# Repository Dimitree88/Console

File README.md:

# CONSOLE — Reference Specification

> Analog mixing console design — full signal-flow reference and
> implementation record. This is a multi-file documentation project;
> this README is the entry point.
>
> **For Claude sessions:** working rules and session-start procedure
> live in `CLAUDE.md`, which is loaded automatically.

---

## What this project is

CONSOLE is a fully analog mixing console. 24 mono input channels,
**4 stereo AUX returns**, 3 stereo groups, 4 AUX masters, CUE master,
Main Mix master with parallel SSL-style bus compression, monitor
section with AFL/PFL solo logic.

Firmware is out of scope; this documents the analog signal flow and
the implementation decisions made during circuit design.

---

## Mental model (one paragraph)

CONSOLE is a 24+4+3 analog desk (24 mono channels, 4 stereo AUX
returns, 3 stereo sub-groups) feeding a Main stereo bus with
parallel SSL-style compression. Channel strips follow a conventional
flow (balanced in → gain → HPF → insert → meter and PFL taps →
MUTE electronic switch → fader → +10 dB post-amp → pan → routing)
with two distinctive design choices: (1) dual balanced inputs A/B
with a full-differential Channel Output from Input A for ADC tracking;
(2) every channel has 4 AUX sends implemented as dual-gang pots that
simultaneously drive a pre-fader and a post-fader mono bus, giving
8 AUX buses total. The 4 stereo AUX returns are routing-only
(no Post-Fader Output to the outside, no Insert, no AUX send) — they
contribute only to internal buses (Main / Groups / AFL / CUE / PFL
stereo). Groups offer per-AUX split-or-mono mode switches so a
stereo group can feed stereo AUX pairs either as L/R split or as
mono premix. The master section's distinguishing features are the
parallel compression on the main bus (dry fader + SSL-style
compressor + wet fader → summed output) and an "in front balance"
pot that mixes an attenuated main mix behind the AFL so the engineer
always hears the context. Digital control is limited to hard-muting /
enabling electronic switches for ACTIVE, SOLO, and AFL — no VCAs,
no recall, no automation. Talkback, tone oscillators, and master
master meters are deliberately absent.

---

## File map

| File | Contents |
|------|----------|
| `CLAUDE.md` | working rules for Claude — required reading at session start, loaded automatically |
| `README.md` | this file — entry point, file map, project status snapshot |
| `00-conventions.md` | design conventions + electrical/implementation conventions (power supplies, grounds, packages, default audio opamp, default topologies for EMI filter, impedance-balanced output, switches+LEDs, …) |
| `01-bus-inventory.md` | enumeration of every bus in the console (stereo + mono) and what feeds each one |
| `02-mono-channel.md` | §2 — mono input channel signal flow + Implementation details (Blocks 1, 2, …) |
| `03-aux-return.md` | §3 — stereo AUX returns (×4, identical) |
| `04-group.md` | §4 — stereo groups (×3) |
| `05-aux-master.md` | §5 — AUX master (×4) |
| `06-cue-master.md` | §6 — CUE master |
| `07-main-mix.md` | §7 — Main Mix master + parallel compression |
| `08-monitor.md` | §8 — Master monitor section |
| `09-not-present.md` | §9 — features deliberately NOT in CONSOLE |
| `10-open-tbd.md` | §10 — items deliberately unresolved at this stage |
| `11-digital-io.md` | §11 — running count of relays, LEDs, and pushbuttons; keep in sync with design changes |

(Sections §11 "Counts" lives at the end of `01-bus-inventory.md`.
The one-paragraph mental model lives at the top of this README.)

---

## Section file structure

Every main section file (`02-mono-channel.md` through `08-monitor.md`)
contains both the **conceptual signal flow** description and an
**Implementation details** subsection. Implementation details grow
over time as concrete circuit choices are made, organized into
"Blocks" (Block 1, Block 2, …) corresponding to chunks of the
signal path that were finalized in a single conversation. The Block
template and editing rules live in `CLAUDE.md`.

---

## Project status snapshot

(Update this section briefly at the end of major conversations, so
future Claude can immediately see where things stand.)

- Mono channel: signal flow conceptually complete. Implementation:
  - Block 1 (input stage → SOURCE switch + DIRECT OUT
    SELECT relay on input PCB) FINALIZED — SOURCE
    relay-driven (AGQ210A03 latching) with momentary pushbutton +
    firmware bipolar pulse; primary motivation: enables global
    master A/B flip across all 24 channels. Channel Output SELECT
    relay added: makes the Channel Output TRS jack switchable between
    Input A full-differential and channel PRE/POST impedance-
    balanced signal (see Block 8).
  - Block 2 (HPF + Insert Send/Return + jack PCB) FINALIZED.
  - Block 3 (meter buffer concept + PFL switch + MUTE) FINALIZED —
    MUTE relay (AGQ210A03) now configured **series + shunt** (contact
    set 1 = series switch, contact set 2 = shunt PRE-FADER to AGND
    when muted), replacing the earlier paralleled-contacts approach.
    Meter buffer implementation (NE5532 + DG419) finalized in Block 10.
  - Block 4 (pre-fader node + fader PCB + post-fader amp +10 dB +
    AUX/CUE pre & post sends) FINALIZED.
  - Block 5 (active pan, Self-style) FINALIZED — Self canonical
    values (R_FB = 2.2 kΩ, center dip ≈ 4.5 dB).
  - Block 6 (post-pan 2-gang × 4-pos routing rotary) topology
    defined; bus summing resistor values TBD together with §04 / §07.
  - Block 7 (AFL switch) FINALIZED — tap at post-pan opamp output;
    NC to AGND (constant termination, click-free); NO to AFL bus.
    Summing resistor values deferred to §08.
  - Block 8 (OUT-PRE/POST switch + switchable Channel Output)
    IN-PROGRESS — 75R taps from pre-MUTE and POST-FADER nodes;
    mechanical PRE-POST selector; 2-pin connector to input PCB;
    Channel Output SELECT relay on input PCB. Front-panel control:
    latching DPDT pushbutton ("DIR/PROC"), sec. 2 → indicator LED
    (LED chain confirmed). Sec. 1 → digital/driver board; MCU GPIO
    or direct-to-driver TBD (see `10-open-tbd.md`). Cold dummy
    network TBD.
  - Block 10 (dual meter buffers) FINALIZED — SOURCE relay
    contact set 2 (wired complementary to set 1) delivers the
    inactive receiver directly to the meter buffer, no additional
    electronic switch; TL072 dual JFET opamp buffers active
    (pre-MUTE) and inactive meter signals; 3-pin connector to meter
    bridge PCB. SOURCE LEDs now MCU GPIO driven (+2 GPIO
    output per channel vs. relay-contact).
- AUX returns: 4 channels, all identical, conceptual stage. ACTIVE
  and AFL switching elements fixed as AGQ210A03 (1 relay
  per function, handling L+R on its two contact sets).
- Groups: same — ACTIVE and AFL fixed as AGQ210A03.
- Master monitor: source-select (§8.1) and Solo summer AFL/PFL
  alternation (§8.2) fixed as AGQ210A03. Other stages still
  conceptual.
- All other sections (AUX/CUE/Main masters): still conceptual.
- Global conventions: established (power, grounds, packages, default
  audio opamp **NE5532**, **standard signal relay
  AGQ210A03** (Panasonic, 1-coil latching, 3 V coil), EMI filter,
  sleeve termination, impedance-balanced output topology,
  front-panel switches with LEDs, per-PCB local bulk decoupling on
  power rails). Selective upgrade to OPA1642 / OPA1656 in specific
  positions is identified as a budget-review item — see
  `10-open-tbd.md`.
- Relay infrastructure: coil supply rail settled (+3.3 V direct);
  driver partitioning settled (per-PCB stackable two-board pattern
  per `00-conventions.md` — audio PCB carries only the relay coil
  via a 3-pin connector, lower stackable PCB carries all logic).
  Total relay count: **112** (24 channels × 4 + 4 AUX returns × 2 +
  3 groups × 2 + 2 master monitor). Coil bipolar driver IC and
  master-output hard-mute for firmware boot init still tracked as
  design-phase open issues in `10-open-tbd.md`.
- Fader PCB partitioning: settled at **2 channels per fader PCB**
  (12 fader PCBs total). Input PCB partitioning still TBD.
- Front-panel channel buttons (§2.11): defined — 4 pushbuttons per
  channel: SOURCE (Pattern B, relay-contact LED), plus
  ACTIVE (orange), SOLO (red), REC (red) all Pattern C
  (integrated LED, MCU GPIO in + out). SOLO drives AFL relay + SIP
  option; REC MIDI-only, no audio relay. Per-channel digital
  I/O: 4 GPIO inputs (buttons) + 3 GPIO outputs (LEDs) +
  relay coil drivers via dedicated ICs.

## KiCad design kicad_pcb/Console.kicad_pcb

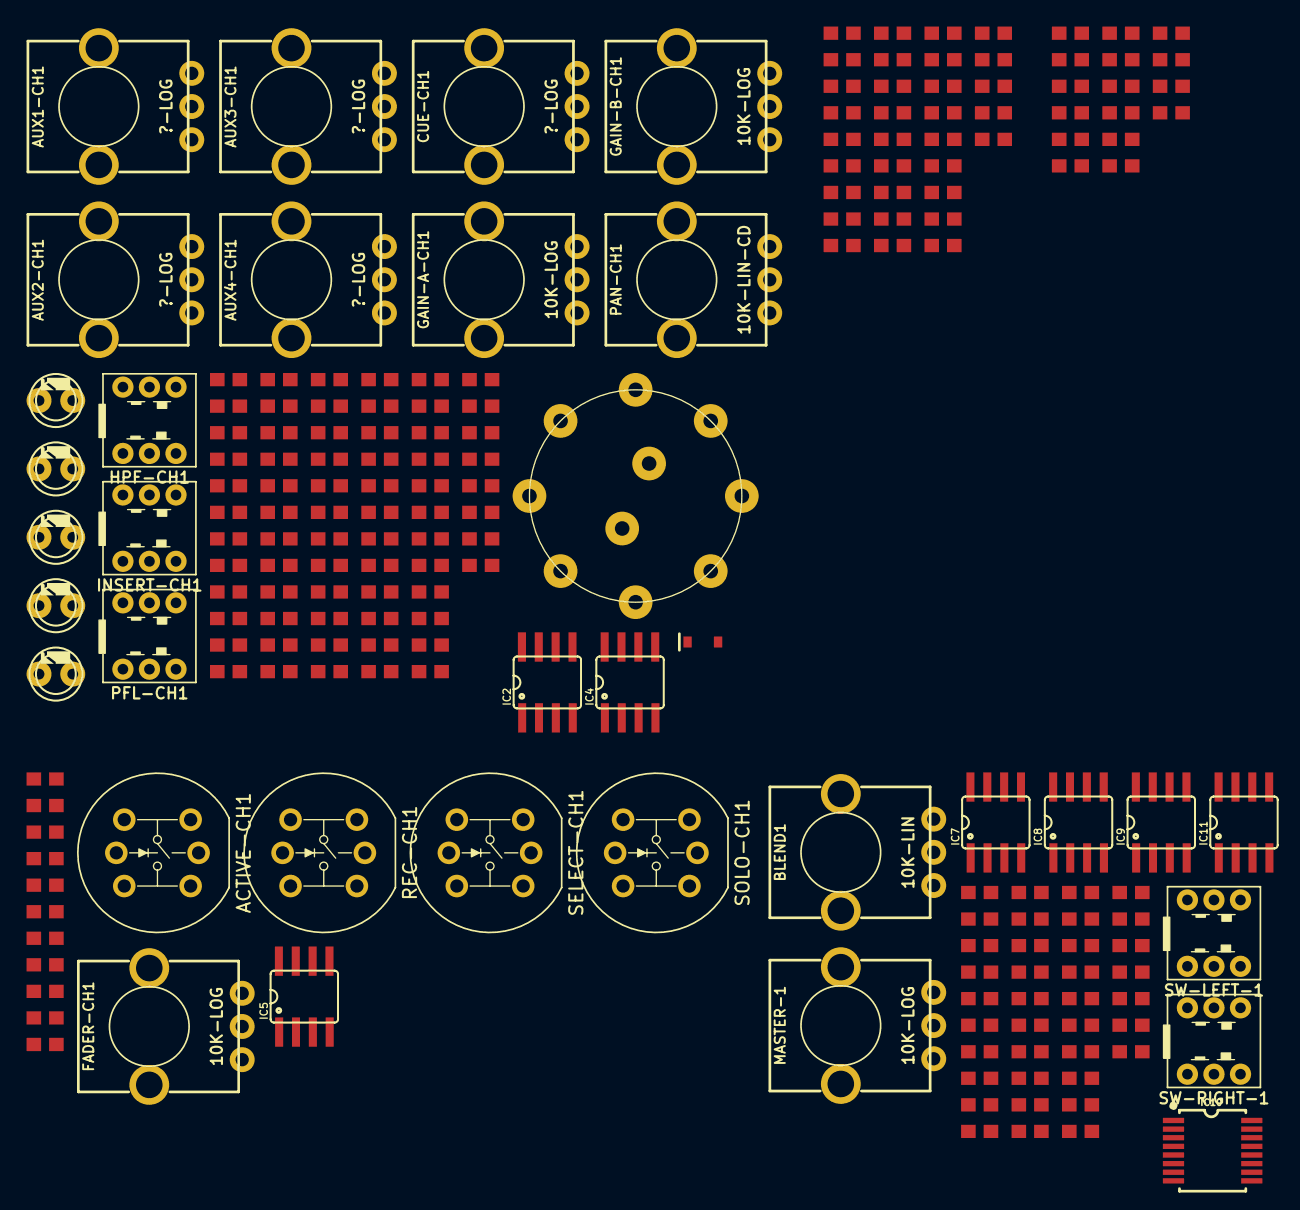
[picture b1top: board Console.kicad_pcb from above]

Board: 2 copper layers, 199 parts (0 on the bottom side), 112 nets, no tracks yet.

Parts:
ACTIVE-CH1: KS-01 yellow; KS-01
AUX1-CH1, AUX2-CH1, AUX3-CH1, AUX4-CH1: ?-LOG; POTENTIOMETER-9MM
BLEND1: 10K-LIN; POTENTIOMETER-9MM
C1, C2, C4, C5, C10, C11, C13, C14, C29, C30, C32, C33, C83, C84, C86, C87, C89, C90, C92, C93: 470pF; 0603
C3, C6, C9, C12, C28, C31, C82, C85, C88, C91: 47pF; 0603
C36, C37, C53: 100pF; 0603
C39, C40, C41: 220nF; 0603
C43, C44, C45, C46, C47, C48, C54, C55, C56, C57, C60, C61, C74, C75, C76, C77: 100nF; 0603
C58, C59: 220pF; 0603
C63, C64, C68, C69, C71: 0603
C80, C81: 47nF; 0603
CUE-CH1: ?-LOG; POTENTIOMETER-9MM
D1: 4148; SOD323
FADER-CH1: 10K-LOG; POTENTIOMETER-9MM
FB1, FB2, FB3, FB4, FB9, FB10, FB11, FB12, FB13, FB14: 330R@100MHz; 0603
GAIN-A-CH1: 10K-LOG; POTENTIOMETER-9MM
GAIN-B-CH1: 10K-LOG; POTENTIOMETER-9MM
HPF-CH1: SWITCH_PUSH_7X7-POLARIZED
IC2, IC4, IC5: NE5532; SO-8
IC7: AD797; SO-8
IC8, IC9: SO-8
IC10: ADG1436; TSSOP-16
IC11: Opamp_Dual; SO-8
INSERT-CH1: SWITCH_PUSH_7X7-POLARIZED
LED-HPF-CH1: orange; LED3MM
LED-INSERT-CH1: blue; LED3MM
LED-MONITOR-A-CH1: red; LED3MM
LED-MONITOR-B-CH1: green; LED3MM
LED-PFL-CH1: red; LED3MM
MASTER-1: 10K-LOG; POTENTIOMETER-9MM
PAN-CH1: 10K-LIN-CD; POTENTIOMETER-9MM
PFL-CH1: SWITCH_PUSH_7X7-POLARIZED
R1, R2, R3, R4: 100K; 0603
R5, R6, R7, R10, R11, R12, R13, R14: 1K; 0603
R8, R15: 100R; 0603
R9, R16, R17, R22, R26, R31, R77, R80, R85, R86: 47K; 0603
R18, R19, R20, R21, R42, R43, R66, R67, R72, R73, R74, R75: 10K; 0603
R23: 5.1K; 0603
R24: 1.3K; 0603
R25: 62K; 0603
R27, R87, R88: 22K; 0603
R28, R29, R78, R79, R81, R82, R89, R92, R93: 75R; 0603
R30, R32, R33, R34, R60, R61, R62, R63, R64: R; 0603
R35: 680R; 0603
R36: 4.7K; 0603
R37, R40, R41, R83, R84: 2.2K; 0603
R38, R39: 3.3K; 0603
R44, R45, R46, R47, R48, R49, R50, R51, R52, R53, R54, R55, R56, R57, R58, R59, R65, R90, R91: 0603
R68, R69, R70, R71: 15K; 0603
R76: 49.9K; 0603
REC-CH1: KS01 red; KS-01
ROUTE-CH1: ROTARY-RS16
SELECT-CH1: KS-01 green; KS-01
SOLO-CH1: KS01 red; KS-01
SW-LEFT-1: SWITCH_PUSH_7X7-POLARIZED
SW-RIGHT-1: SWITCH_PUSH_7X7-POLARIZED

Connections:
+5VD: HPF-CH1.2-C (C), INSERT-CH1.2-C (C), PFL-CH1.2-C (C)
+15V: C44.1, C45.1, C47.1, C54.1, C56.1, C60.1, C74.1, C76.1, IC2.8 (V+), IC4.8 (V+), IC5.8 (V+), IC7.7 (V+), IC8.8 (V+), IC9.8 (V+)
-15V: C43.2, C46.2, C48.2, C55.2, C57.2, C61.2, C75.2, C77.2, IC2.4 (V-), IC4.4 (V-), IC5.4 (V-), IC7.4 (V-), IC8.4 (V-), IC9.4 (V-)
GND: AUX1-CH1.1 (CCW), AUX2-CH1.1 (CCW), AUX3-CH1.1 (CCW), AUX4-CH1.1 (CCW), BLEND1.2 (WIPER), C37.2, C43.1, C44.2, C45.2, C46.1, C47.2, C48.1, C54.2, C55.1, C56.2, C57.1, C60.2, C61.1, C68.2, C74.2, C75.1, C76.2, C77.1, CUE-CH1.1 (CCW), FADER-CH1.1, IC7.3 (+), IC8.3 (+), IC8.5 (+), PAN-CH1.3 (CW), PFL-CH1.1-NC (NC), R1.2, R2.2, R3.2, R4.2, R9.2, R16.2, R17.2, R21.2, R22.2, R23.2, R25.2, R26.2, R31.2, R37.2, R42.1, R43.1, R74.2, R77.2, R80.2, R85.2, R86.2
GNDD: ACTIVE-CH1.SW-B, R30.2, R32.2, R33.2, R34.2, R60.2, R61.2, R62.2, R63.2, R64.2, REC-CH1.SW-B, SELECT-CH1.SW-B, SOLO-CH1.SW-B
GND_CHASSIS: C3.2, C6.2, C9.2, C12.2, C28.2, C31.2, C82.2, C85.2, C88.2, C91.2
LEFT-OUT: IC11.1, IC11.2 (-), R87.2
unnamed: C2.2, FB2.1
unnamed: C1.1, FB1.1
unnamed: ACTIVE-CH1.LED-C, R61.1
unnamed: AUX1-CH1.3 (CW), AUX2-CH1.3 (CW), AUX3-CH1.3 (CW), AUX4-CH1.3 (CW), CUE-CH1.3 (CW)
unnamed: AUX1-CH1.2 (WIPER), R48.2
unnamed: AUX2-CH1.2 (WIPER), R54.2
unnamed: AUX3-CH1.2 (WIPER), R56.2
unnamed: AUX4-CH1.2 (WIPER), R58.2
unnamed: C11.2, FB4.1
unnamed: C10.1, FB3.1
unnamed: BLEND1.1 (CCW), R70.1, R71.2
unnamed: BLEND1.3 (CW), R68.2, R69.1
unnamed: C90.2, FB14.1
unnamed: C89.1, FB13.1
unnamed: C1.2, C2.1, C3.1
unnamed: C4.1, FB1.2
unnamed: C4.2, C5.1, C6.1
unnamed: C5.2, FB2.2
unnamed: C9.1, C10.2, C11.1
unnamed: C12.1, C13.2, C14.1
unnamed: C13.1, FB3.2
unnamed: C14.2, FB4.2
unnamed: R17.1, R29.1
unnamed: C28.1, C29.2, C30.1
unnamed: C29.1, FB9.1
unnamed: C30.2, FB10.1
unnamed: C31.1, C32.2, C33.1
unnamed: C36.2, IC2.1, R20.1
unnamed: C39.2, C40.1, R23.1
unnamed: C40.2, C41.1, R24.1
unnamed: C53.2, R35.1, R36.1
unnamed: C63.2, IC7.6, R65.1, R66.2
unnamed: C64.2, IC8.1, R67.1
unnamed: R69.2, R78.2
unnamed: C69.2, IC9.1, R75.1
unnamed: C71.2, IC8.7, R76.1
unnamed: R77.1, R81.1
unnamed: R80.1, R82.1
unnamed: C80.1, R87.1
unnamed: C81.1, R88.1
unnamed: C82.1, C83.2, C84.1
unnamed: C83.1, FB11.1
unnamed: C84.2, FB12.1
unnamed: C85.1, C86.2, C87.1
unnamed: C88.1, C89.2, C90.1
unnamed: C91.1, C92.2, C93.1
unnamed: C92.1, FB13.2, R92.1
unnamed: C93.2, FB14.2, R93.1
unnamed: CUE-CH1.2 (WIPER), R90.2
unnamed: GAIN-A-CH1.2, GAIN-A-CH1.3, R8.2
unnamed: GAIN-B-CH1.2, GAIN-B-CH1.3, R15.2
unnamed: HPF-CH1.1-C (C), INSERT-CH1.1-NC (NC), R28.1
unnamed: C39.1, HPF-CH1.1-NC (NC)
unnamed: HPF-CH1.1-NO (NO), R26.1
unnamed: R6.1, R7.2
unnamed: R12.1, R13.2
unnamed: R5.1, R6.2
unnamed: GAIN-A-CH1.1, R7.1, R10.1
unnamed: R11.1, R12.2
unnamed: GAIN-B-CH1.1, R13.1, R14.1
unnamed: C37.1, IC2.3 (+), R19.1, R21.1
unnamed: C36.1, IC2.2 (-), R18.1, R20.2
unnamed: C41.2, IC2.5 (+), R25.1
unnamed: IC2.6 (-), IC2.7, R24.2
unnamed: C58.1, IC4.3 (+), PAN-CH1.2 (WIPER), R38.2
unnamed: IC4.2 (-), R40.1, R42.2
unnamed: C59.1, IC4.5 (+), R39.2
unnamed: IC4.6 (-), R41.1, R43.2
unnamed: IC5.1, R35.2
unnamed: IC5.3 (+), R31.1
unnamed: C53.1, IC5.2 (-), R36.2, R37.1
unnamed: C63.1, IC7.2 (-), R65.2
unnamed: C64.1, IC8.2 (-), R66.1, R67.2
unnamed: C71.1, IC8.6 (-), R68.1, R71.1, R76.2
unnamed: C68.1, IC9.3 (+), R73.1, R74.1
unnamed: C69.1, IC9.2 (-), R72.1, R75.2
unnamed: C80.2, IC11.3 (+), R83.1, R85.1, SW-LEFT-1.2-NO (NO), SW-RIGHT-1.2-C (C)
unnamed: C81.2, IC11.5 (+), R84.1, R86.1, SW-LEFT-1.2-C (C), SW-RIGHT-1.2-NO (NO)
unnamed: INSERT-CH1.1-C (C), R27.1, R89.2
unnamed: INSERT-CH1.1-NO (NO), R22.1
unnamed: C32.1, FB9.2
unnamed: C33.2, FB10.2
unnamed: C86.1, FB11.2
unnamed: C87.2, FB12.2
unnamed: PFL-CH1.1-C (C), R27.2
unnamed: R44.2, ROUTE-CH1.1
unnamed: R46.2, ROUTE-CH1.2
unnamed: R50.2, ROUTE-CH1.3
unnamed: R52.2, ROUTE-CH1.4
unnamed: R62.1, SOLO-CH1.LED-C
unnamed: R63.1, SELECT-CH1.LED-C
unnamed: R64.1, REC-CH1.LED-C
unnamed: C58.2, IC4.1, R38.1, R40.2, ROUTE-CH1.A (C)
unnamed: R45.2, ROUTE-CH1.5 (1)
unnamed: R47.2, ROUTE-CH1.6 (2)
unnamed: R51.2, ROUTE-CH1.7 (3)
unnamed: R53.2, ROUTE-CH1.8 (4)
unnamed: C59.2, IC4.7, R39.1, R41.2, ROUTE-CH1.B (C)
unnamed: R81.2, SW-LEFT-1.1-C (C)
unnamed: SW-LEFT-1.1-NC (NC), SW-RIGHT-1.2-NC (NC)
unnamed: R83.2, SW-LEFT-1.1-NO (NO)
unnamed: SW-LEFT-1.2-NC (NC), SW-RIGHT-1.1-NC (NC)
unnamed: R82.2, SW-RIGHT-1.1-C (C)
unnamed: R84.2, SW-RIGHT-1.1-NO (NO)
RIGHT-OUT: IC11.6 (-), IC11.7, R88.2

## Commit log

2026-04-26 update 1
2026-04-28 update 2
2026-05-02 added pcb
2026-05-02 relay instead of switch
2026-05-08 altro
2026-05-08 claude
2026-05-13 kicad10
2026-05-14 modifiche sostanziali al path
2026-05-14 altre modifiche
2026-05-14 altre cose
2026-05-14 vscode settings
2026-05-15 fx bypass
2026-05-15 metering
2026-05-15 bom fix
2026-05-15 bom addition
2026-05-15 varie
2026-05-17 fix varie
2026-05-17 fix bom
2026-05-17 altri appunti
